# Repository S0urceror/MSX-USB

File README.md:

# MSX-USB
## Some history
In the 80's the MSX standard was created by Kazuhiko Nishi. He envisioned a simple yet powerful home computer based on standard hardware, software (BIOS/MSX DOS) and connectivity. From 1983 to 1990 manufacturers, like Philips, Sony, Yamaha, Sharp, Canon and many more, made computers according to this standard.

Because of the fact that extensibility was part of the standard people could design cartridges that would add synthesizer sound, memory, modems, rom-based games, or combinations of the above.

Cartridges were connected via a standard 50pin connector that remained the same accross 4 generations of MSX (1/2/2+/TurboR). BIOS and MSX-DOS were designed in a way to discover these via rom-based drivers, software hooks, extended bios.

Standardisation offers a big advantage because everything that adheres to the standard can connect to it.

## USB
USB was designed in the 90's to do something similar. To standardize the connection of peripherals to personal computers, both to communicate with and to supply electric power. It has now largely replaced interfaces such as serial ports and parallel ports, and has become commonplace on a wide range of devices. Like USB flash drives, keyboards, mice, wifi, serial, camera's, etc.

What if the MSX would have an USB connection? And if the BIOS/MSX DOS would automatically recognize devices connected to it?

## Meet MSX-USB
Inspired by the work of Xavirompe and his [RookieDrive](http://rookiedrive.com/en/) I set out to do exactly this. And since I'm a big believer of open standards and open source I'm opening up my work to everyone.

On this GitHub page you can find:
* Schematics (KiCAD), that interfaces a cheap USB CH376s board to the MSX cartridge port.
* Drivers, currently Flash drives on Nextor and HID keyboards are supported.
* Debugging tools, to connect a test board to your PC/MAC and assist in debugging.

On my GitHub I also have forks of OpenMSX and CocoaMSX that either emulate or connect to a test board via serial to assist in development and debugging.

## Schematics
This connects the CH376s board you can find on eBay or AliExpress for around 4 Euro to the MSX. 

Circuitry is added to correctly handle the _BUSDIR signal. Make sure you select parallel by setting the jumper on the CH376s board correctly.

The CH376s board will be visible on port 10h and 11h on the MSX. Port 11h is the command port and 10h is the data port. Specifics on how to program for the CH376s are scattered around the Internet:
* https://www.mpja.com/download/ch376ds1.pdf
* https://arduinobasics.blogspot.com/2015/05/ch376s-usb-readwrite-module.html

Most information is available on how to use the higher-order API for flash drives. 

If you want to use other USB devices you have to go low-level. As it turns out Konamiman already did some work there and after some researching I got USB HID Keyboards, Ethernet, Serial working as well. Check out my source-code or these great pages for more information:
* http://www.usbmadesimple.co.uk/index.html
* https://www.beyondlogic.org/usbnutshell/usb1.shtml

## PCB
Please use the rev4 PCB by @cristianoag. This fits in a Konami style cartridge case and has a switch to select between two ROM images. Also use the rev4 CPLD code to enable this feature.

## UNAPI USB
I wrote a UNAPI USB specification and implemented the Usb Host driver according to this. The next version of this Host driver will also implement the Usb Hub specification and enumerate and initialise all devices connected.

## USB HID Keyboard
The Usb Keyboard driver connects to Unapi Usb driver and hooks itself to H.CHGE. From that moment on it replaces your trusted MSX keyboard by a shiny new USB Keyboard. Or a wireless one if you have inserted the appropriate Logitech receiver.

## USB CDC ECM Ethernet
The USB CDC ECM Ethernet driver is finished. It uses the Unapi USB and conforms to the Unapi Ethernet standard. Internestor Lite can now connect and use your USB Ethernet device. Please note that currently we only support USB CDC ECM. Make sure your Ethernet device supports this.

All USB Ethernet devices built around the **RTL8153** chipset support USB CDC ECM. They usually cost around 20 euro.

## USB Storage
A low level USB driver is created to connect to storage devices like thumb drives, portable hard disks, etc. 

## USB Hub
The USB Hub driver will interrogate an USB Hub and all devices connected to it.

# Installation instructions
Check [this page](INSTALL.md) for installation instructions and links to the various binaries that have been developed.

# Build your own (DIY)
Check [this page](DIY.md) for information on how to make the PCB, program the CPLD device, flash the ROM, etc.

# Collaboration
Do you want to help with the development of MSX USB? Write drivers for other devices? Or contribute in other ways?

Please drop me line on sourceror at neximus.nl or meet me on the msx.org forum.

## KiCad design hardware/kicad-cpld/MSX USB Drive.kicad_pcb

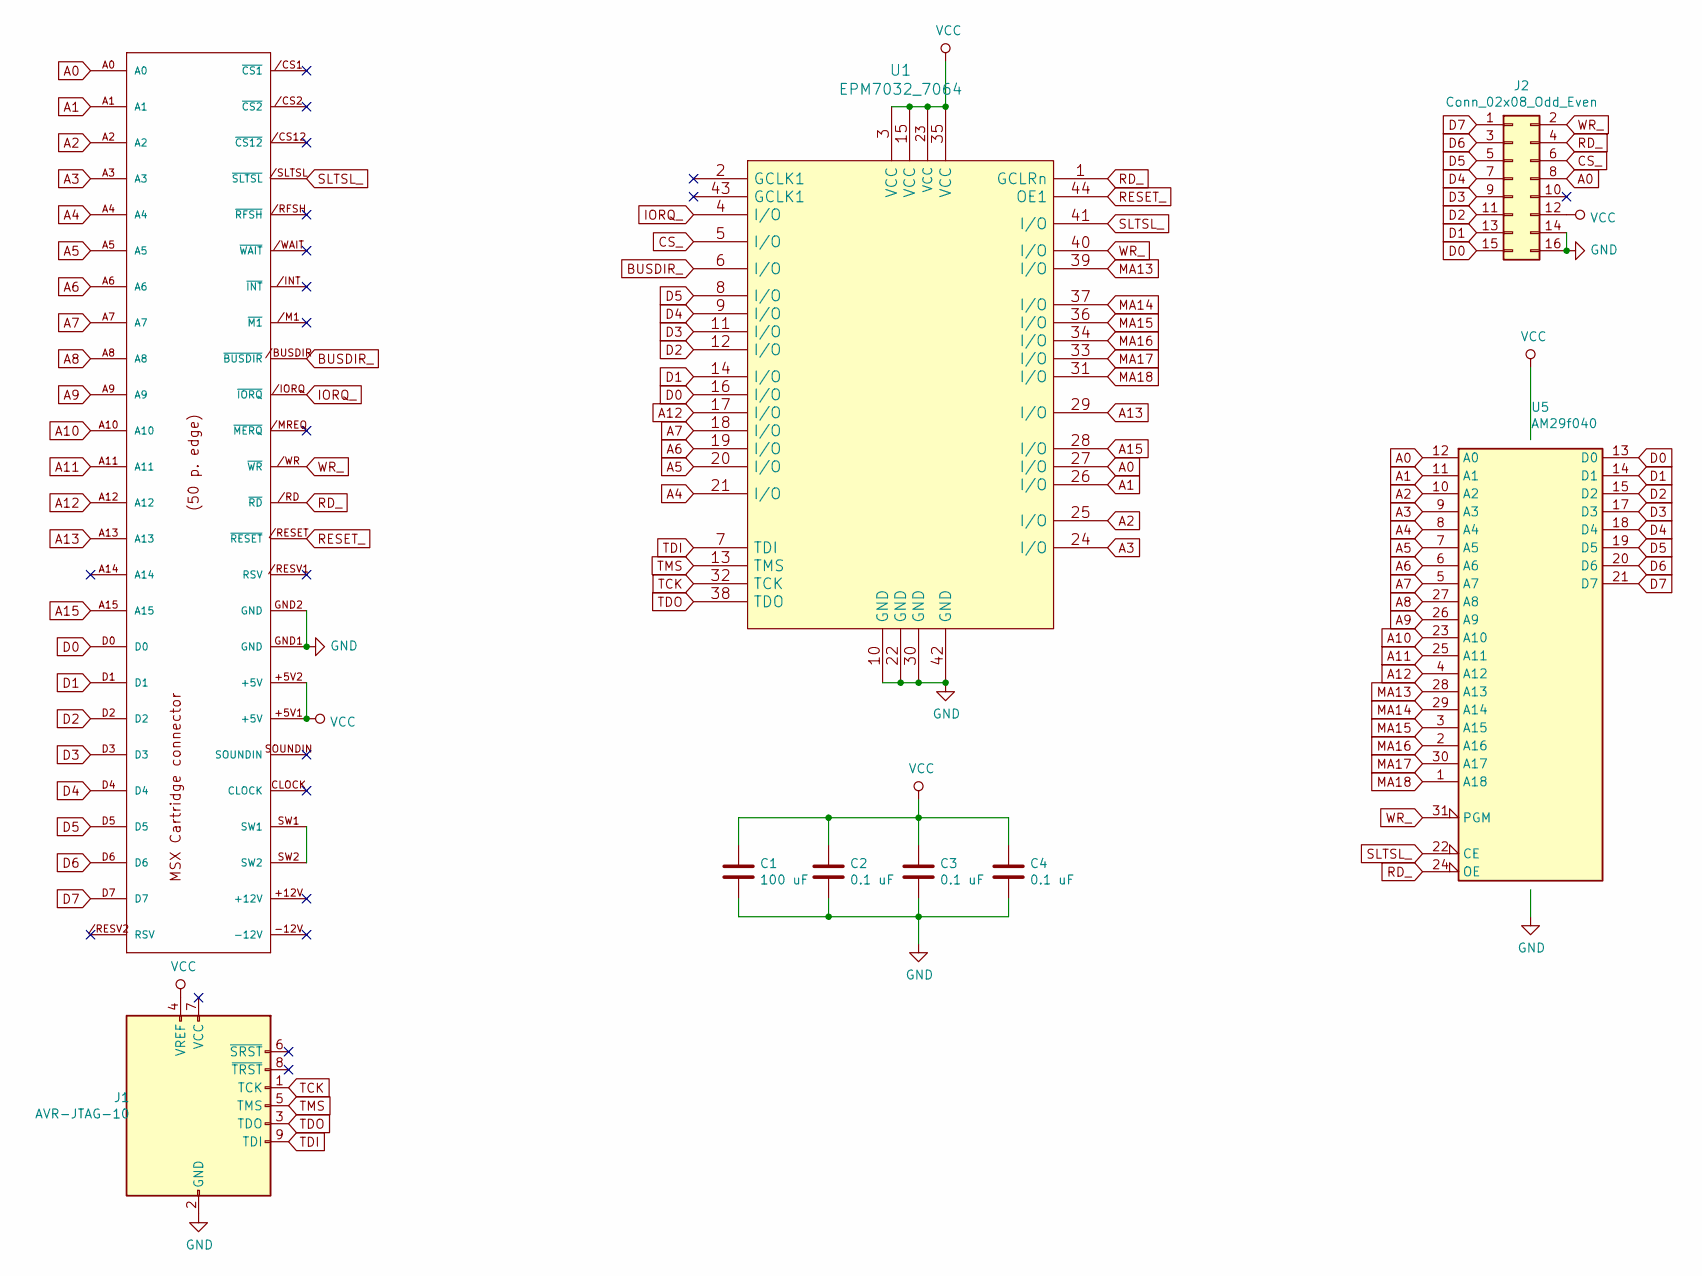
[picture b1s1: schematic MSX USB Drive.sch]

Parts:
C1: 100 uF; CP_Elec_6.3x5.4
C2, C3, C4: 0.1 uF; C_0805_2012Metric_Pad1.15x1.40mm_HandSolder
EDG1: MSX_CON; msx-con-MSXCART
J1: AVR-JTAG-10; PinHeader_2x05_P2.54mm_Vertical
J2: Conn_02x08_Odd_Even; PinHeader_2x08_P2.54mm_Vertical
U1: EPM7032_7064; PLCC44
U5: AM29f040; DIP-32_W15.24mm_Socket

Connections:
A0: EDG1.A0, J2.8, U1.27 (I/O), U5.12 (A0)
A1: EDG1.A1, U1.26 (I/O), U5.11 (A1)
A2: EDG1.A2, U1.25 (I/O), U5.10 (A2)
A3: EDG1.A3, U1.24 (I/O), U5.9 (A3)
A4: EDG1.A4, U1.21 (I/O), U5.8 (A4)
A5: EDG1.A5, U1.20 (I/O), U5.7 (A5)
A6: EDG1.A6, U1.19 (I/O), U5.6 (A6)
A7: EDG1.A7, U1.18 (I/O), U5.5 (A7)
A8: EDG1.A8, U5.27 (A8)
A9: EDG1.A9, U5.26 (A9)
A10: EDG1.A10, U5.23 (A10)
A11: EDG1.A11, U5.25 (A11)
A12: EDG1.A12, U1.17 (I/O), U5.4 (A12)
A13: EDG1.A13, U1.29 (I/O)
A15: EDG1.A15, U1.28 (I/O)
BUSDIR_: EDG1./BUSDIR (~BUSDIR), U1.6 (I/O)
CS_: J2.6, U1.5 (I/O)
D0: EDG1.D0, J2.15, U1.16 (I/O), U5.13 (D0)
D1: EDG1.D1, J2.13, U1.14 (I/O), U5.14 (D1)
D2: EDG1.D2, J2.11, U1.12 (I/O), U5.15 (D2)
D3: EDG1.D3, J2.9, U1.11 (I/O), U5.17 (D3)
D4: EDG1.D4, J2.7, U1.9 (I/O), U5.18 (D4)
D5: EDG1.D5, J2.5, U1.8 (I/O), U5.19 (D5)
D6: EDG1.D6, J2.3, U5.20 (D6)
D7: EDG1.D7, J2.1, U5.21 (D7)
GND: C1.2, C2.2, C3.2, C4.2, EDG1.GND1 (GND), EDG1.GND2 (GND), J1.2 (GND), J1.10 (GND), J2.14, J2.16, U1.10 (GND), U1.22 (GND), U1.30 (GND), U1.42 (GND), U5.16 (GND)
IORQ_: EDG1./IORQ (~IORQ), U1.4 (I/O)
MA13: U1.39 (I/O), U5.28 (A13)
MA14: U1.37 (I/O), U5.29 (A14)
MA15: U1.36 (I/O), U5.3 (A15)
MA16: U1.34 (I/O), U5.2 (A16)
MA17: U1.33 (I/O), U5.30 (A17)
MA18: U1.31 (I/O), U5.1 (A18)
unnamed: EDG1.SW1, EDG1.SW2
RD_: EDG1./RD (~RD), J2.4, U1.1 (GCLRn), U5.24 (OE)
RESET_: EDG1./RESET (~RESET), U1.44 (OE1)
SLTSL_: EDG1./SLTSL (~SLTSL), U1.41 (I/O), U5.22 (CE)
TCK: J1.1 (TCK), U1.32 (TCK)
TDI: J1.9 (TDI), U1.7 (TDI)
TDO: J1.3 (TDO), U1.38 (TDO)
TMS: J1.5 (TMS), U1.13 (TMS)
VCC: C1.1, C2.1, C3.1, C4.1, EDG1.+5V1 (+5V), EDG1.+5V2 (+5V), J1.4 (VREF), J2.12, U1.3 (VCC), U1.15 (VCC), U1.23 (VCC), U1.35 (VCC), U5.32 (VCC)
WR_: EDG1./WR (~WR), J2.2, U1.40 (I/O), U5.31 (PGM)

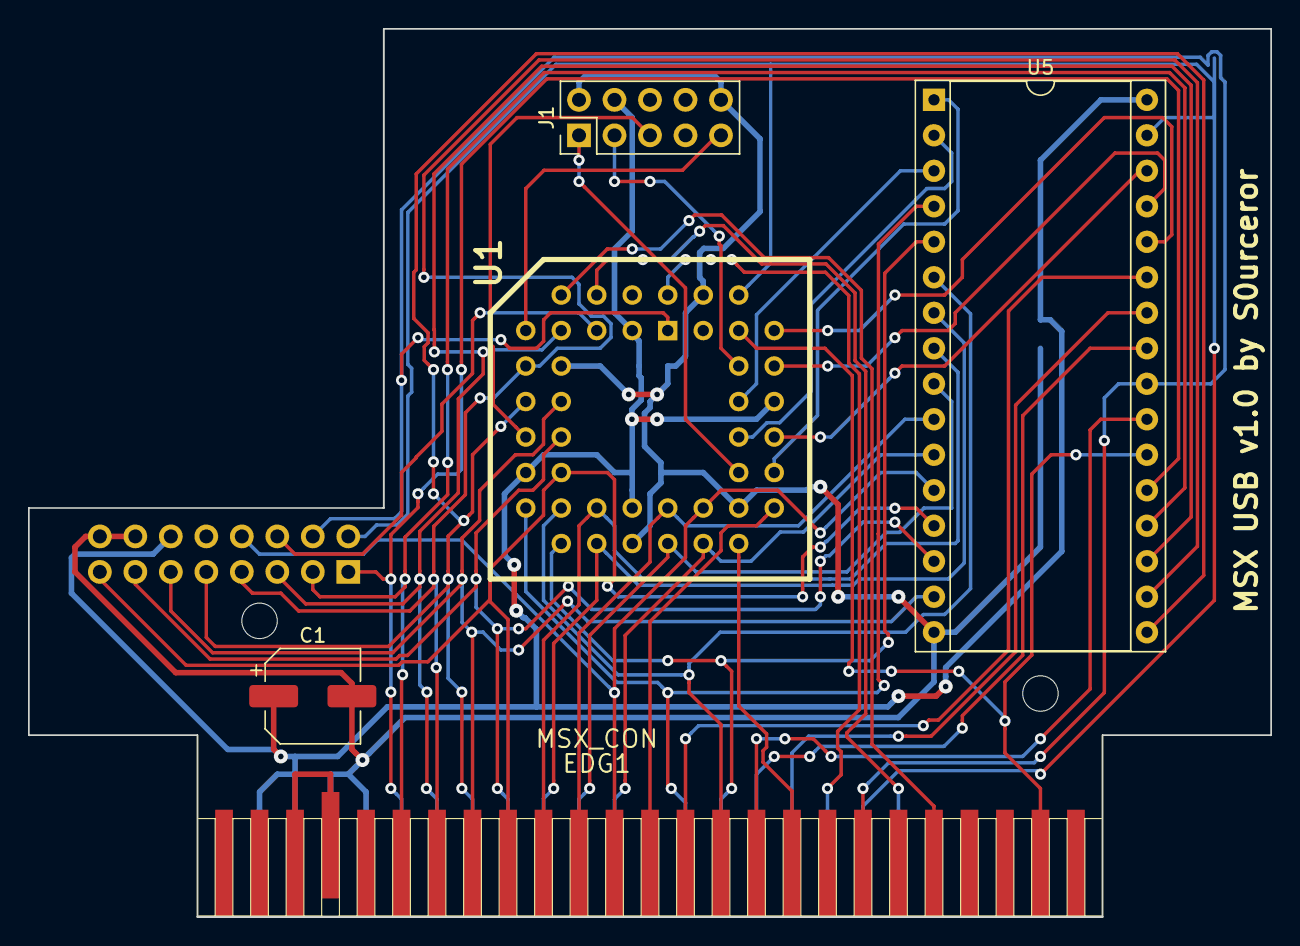
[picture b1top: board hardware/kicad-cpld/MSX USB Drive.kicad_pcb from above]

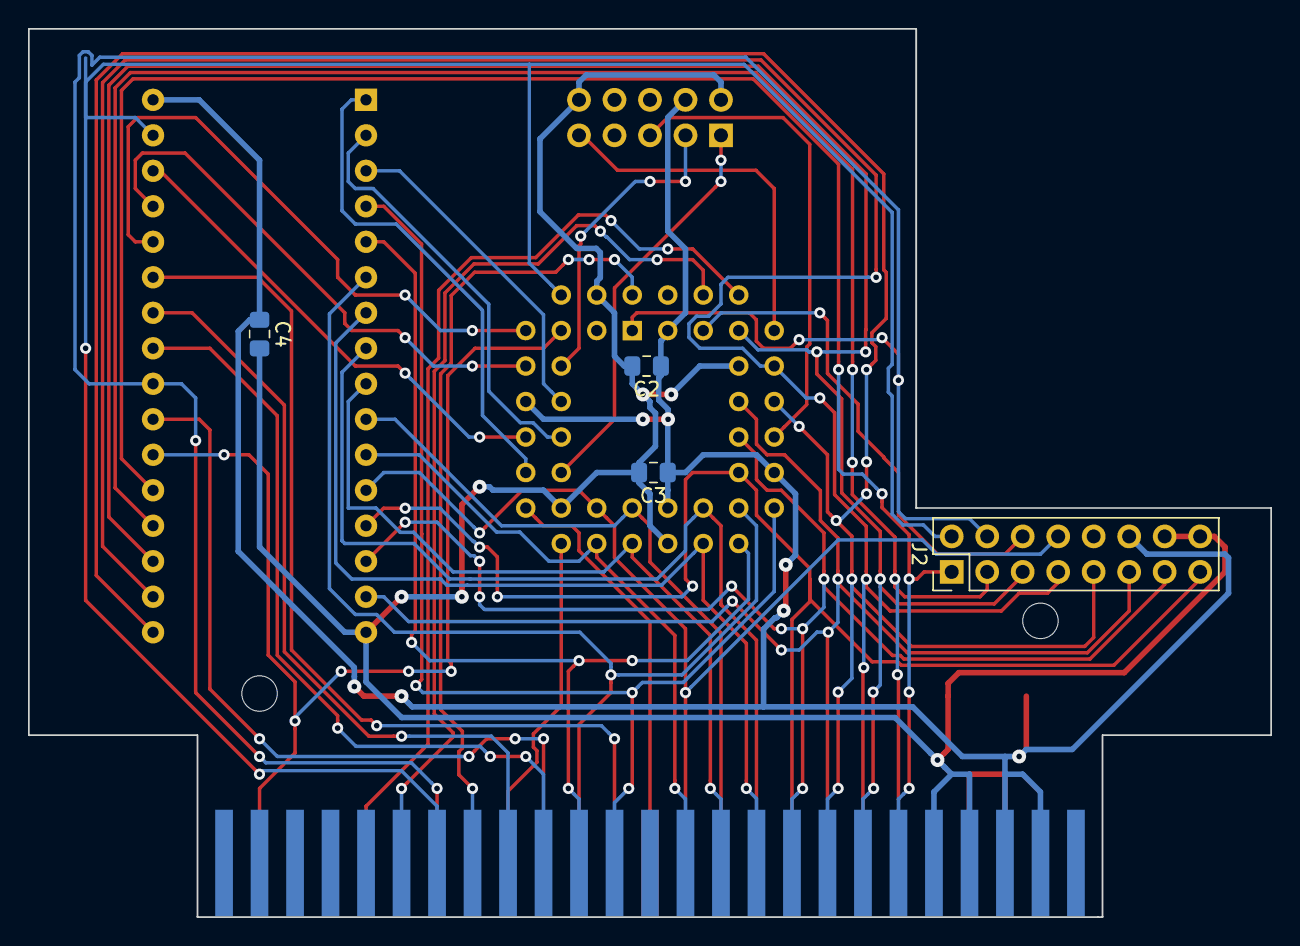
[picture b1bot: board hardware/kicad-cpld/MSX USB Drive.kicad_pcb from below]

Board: 2 copper layers, 88.9 x 63.6 mm, 9 parts (4 on the bottom side), 43 nets.

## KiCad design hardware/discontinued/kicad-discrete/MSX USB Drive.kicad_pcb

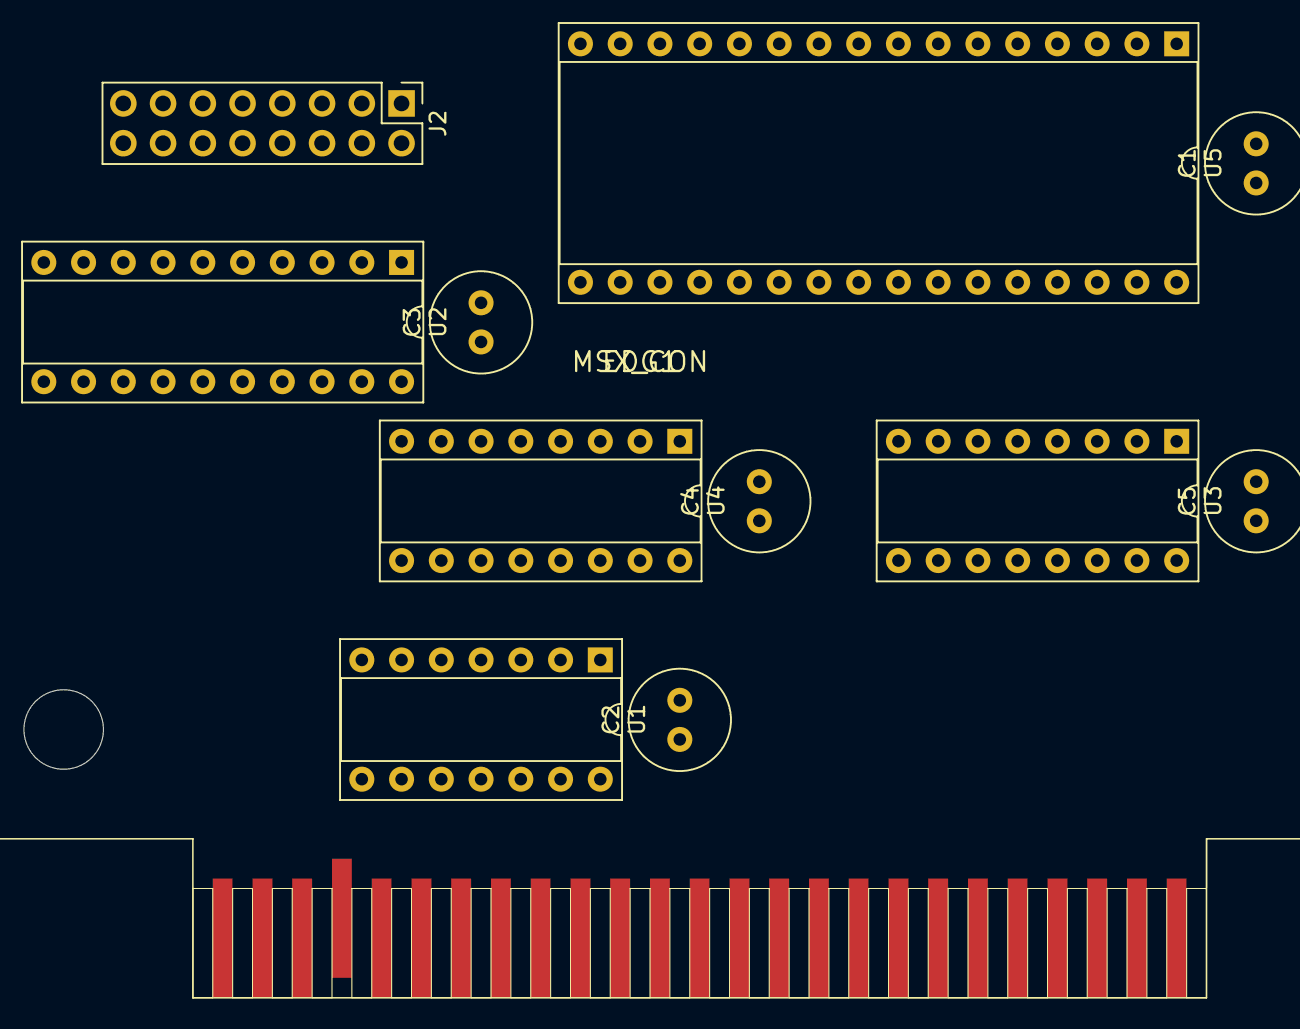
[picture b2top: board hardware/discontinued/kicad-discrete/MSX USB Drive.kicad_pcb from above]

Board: 2 copper layers, 12 parts (0 on the bottom side), 39 nets, no tracks yet.

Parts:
C1, C2, C3, C4, C5: 0.1 uF; C_Radial_D6.3mm_H5.0mm_P2.50mm
EDG1: MSX_CON; msx-con-MSXCART
J2: Conn_02x08_Odd_Even; PinHeader_2x08_P2.54mm_Vertical
U1: 74LS32; DIP-14_W7.62mm_Socket
U2: 74LS688; DIP-20_W7.62mm_Socket
U3, U4: 74LS670; DIP-16_W7.62mm_Socket
U5: SST39SF040; DIP-32_W15.24mm_Socket

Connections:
A0: EDG1.A0, J2.8, U5.12
A1: EDG1.A1, U2.2, U5.11
A2: EDG1.A2, U2.4, U5.10
A3: EDG1.A3, U2.6, U5.9
A4: EDG1.A4, U2.17, U5.8
A5: EDG1.A5, U2.8, U5.7
A6: EDG1.A6, U2.11, U5.6
A7: EDG1.A7, U2.13, U5.5
A8: EDG1.A8, U5.27
A9: EDG1.A9, U5.26
A10: EDG1.A10, U5.23
A11: EDG1.A11, U5.25
A12: EDG1.A12, U5.4
A13: EDG1.A13, U3.4, U3.13, U4.4, U4.13
A15: EDG1.A15, U3.5, U3.14, U4.5, U4.14
BUSDIR_: EDG1./BUSDIR, U1.6
CS_: J2.6, U1.4, U2.19
D0: EDG1.D0, J2.15, U3.15, U5.13
D1: EDG1.D1, J2.13, U3.1, U5.14
D2: EDG1.D2, J2.11, U3.2, U5.15
D3: EDG1.D3, J2.9, U3.3, U5.17
D4: EDG1.D4, J2.7, U4.15, U5.18
D5: EDG1.D5, J2.5, U4.1, U5.19
D6: EDG1.D6, J2.3, U4.2, U5.20
D7: EDG1.D7, J2.1, U4.3, U5.21
GND: C1.2, C2.2, C3.2, C4.2, C5.2, EDG1.GND1, EDG1.GND2, J2.14, J2.16, U1.1, U1.2, U1.7, U1.9, U1.10, U2.1, U2.3, U2.5, U2.7, U2.9, U2.10, U2.12, U2.14, U2.16, U3.8, U3.11, U4.8, U4.11, U5.16
IORQ_: EDG1./IORQ, U2.15
unnamed: EDG1.SW1, EDG1.SW2
unnamed: U1.11, U3.12
unnamed: U3.6, U5.2
unnamed: U3.7, U5.3
unnamed: U3.9, U5.29
unnamed: U3.10, U5.28
unnamed: U4.9, U5.1
unnamed: U4.10, U5.30
RD_: EDG1./RD, J2.4, U1.5, U5.22
SLTSL_: EDG1./SLTSL, U1.13, U5.24
VCC: C1.1, C2.1, C3.1, C4.1, C5.1, EDG1.+5V1, EDG1.+5V2, J2.12, U1.14, U2.18, U2.20, U3.16, U4.16, U5.32
WR_: EDG1./WR, J2.2, U1.12, U5.31

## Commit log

2020-01-21 Initial combined MSX USB release
2020-01-21 minor changes in readme
2020-01-23 Updated VSCode Build System
2020-01-23 dist folder README's
2020-01-23 Updated README's
2020-02-03 re-organised files, added special chars
2020-02-12 1st release MSX USB UNAPI + lsusb client
2020-02-12 minor updates
2020-02-13 Updated USB UNAPI specification
2020-02-16 Implemented JumpTable within UNAPI driver
2020-02-16 Implemented Jumptable
2020-02-22 UNAPI compatible keyboard driver
2020-02-22 Updates to support UNAPI USB keyboard
2020-02-22 Updated GPL T&C's
2020-03-02 USB Ethernet and Hub supported
2020-03-02 Rearranged folders and updated README's
2020-03-15 USB Ethernet working
2020-03-26 squashed bugs and made it faster
2020-03-26 Updated schematics with the right gate in 74LS32
2020-03-26 Added A13,A15 and updated IC numbering
2020-03-26 PCB first attempt
2020-04-06 CPLD version of PCB + verilog code
2020-04-07 Upload all binaries
2020-04-07 Added installation instructions
2020-04-08 Linked all binaries to installation instructions
2020-04-08 NEXTOR.DSK is default
2020-04-08 Added .dsk files for USB flashdrive
2020-04-08 Added DSK images for USB flashdrive
2020-04-08 remove rubbish
2020-04-08 remove .DS_Store
2020-04-08 .DS_Store banished!
2020-04-09 Updated install instructions
2020-04-11 RESET_ALL first
2020-04-11 Added link to disk images ZIP
2020-04-11 now pointing to the raw file
2020-04-11 Updated the CH_RESET routine
2020-04-11 combined drivers, updated reset
2020-04-11 new binaries
2020-04-13 Combined USB Host and Nextor driver
2020-04-13 wait timers implemented
2020-04-13 fixed bugs in Basic extensions
2020-04-19 Bugfixes after merge of USBHost and Nextor
2020-04-26 NXT_DIRECT implemented
2020-04-28 latest lsusb.com
2020-04-28 latest nextor.rom
2020-04-28 ethernet + keyboard updated and operational
2020-04-28 Updated the README and INSTALL instructions
2020-04-28 Usb Hub work has started...
2020-05-14 CPLD PCB Verilog + Flash software works
2020-05-16 working on Hub
2020-05-22 USB Hub, Ethernet and Keyboard working
2020-05-22 RookieDrive build of MSXUSB
2020-05-22 Updated Installation instructions for RookieDrive and Flash
2020-05-22 Small update on RookieDrive mention in Install instructions
2020-05-23 remove test files
2020-06-04 UsbStorage low-level driver completed
2020-06-13 Bugfixing, USB keyboard updated
2020-06-13 Flash.com supports SST39F040
2020-06-13 Update flash.com to recognize 39SF010 and 39SF020
2020-06-15 Updated driver inititialisation + bugfixes
2020-06-15 Reset before check to recover from hanging USB
2020-06-15 Added /T and /Sx arguments to Flash utility
2020-06-16 Discrete PCB discontinued, flash changed AM29F040
2020-06-19 Added Flash ROM support
2020-06-21 RookieDrive version + Disk ROM (complete)
2020-06-23 Update issue templates
2020-10-18 uIP + various bug fixes
2020-10-18 Updated copyright messages
2021-03-27 SPI and MiSTer support
2021-03-27 normal int's for when not SPI
2021-03-30 emulate parallel interface via SPI
2021-04-06 noobtocol SPI emulating parallel
2021-05-26 mapper tester
2021-05-30 flash support AMIC, new v1.0 Gerbers
2021-08-31 Various bugfixed, updated documentation
2022-01-11 Stability improvements, STALL handling
2022-01-31 stability, first release msxusbnext
2022-01-31 cleanup
2022-02-05 msxusbnext updates
2022-02-06 CALL mountdsk for MSXUSBNext
2022-02-09 fixed get_string2
2022-02-09 v0.3 MSXUSBNext supports _MOUNTDSK
2022-02-19 MSXUSBNext now supports AUTOEXEC.DSK
2022-02-20 v0.4 handle not valid keypresses in menu
2022-02-23 Port to linux
2022-03-13 Fixed STALL recovery
2022-06-29 Fix for the folder issue
2022-06-29 Fix for the issue with change directories
2022-06-30 Temp solution
2022-06-30 Temp solution for the chdir issue
2022-08-19 Fixed bug raised by @christianoag
2022-08-21 recompiled with sdcc 4.1.0, not yet compatible with 4.2.0
2022-09-04 MSXUSBNext minor tweaks, cleanup
2022-09-11 Nextor 2.1.1 build
2022-09-11 Nextor 2.1.1 build - fix
2022-09-11 Nextor bug patched in DOS1 mode, page 1 RW
2022-10-05 PCB rev3
2022-10-08 Verilog changes to support the flash selection toggle
2022-10-10 Interactive BOM
2022-10-25 Rev4
2022-10-25 small adjust on c1
2022-10-25 Reverting the not on the selection bit as the circuit is 0 by default for the switch
2022-11-27 added rev4 pcb by @cristianoag
2022-11-27 added flash-switching by @cristianoag
2022-11-27 removed test code
2022-11-27 Updated readme to mention rev4 PCB by @cristianoag
2023-01-13 small changes to the PCB (holes) and cpld code
2023-01-13 It is CPLD code, not FPGA
2023-05-08 FDD capable firmware
